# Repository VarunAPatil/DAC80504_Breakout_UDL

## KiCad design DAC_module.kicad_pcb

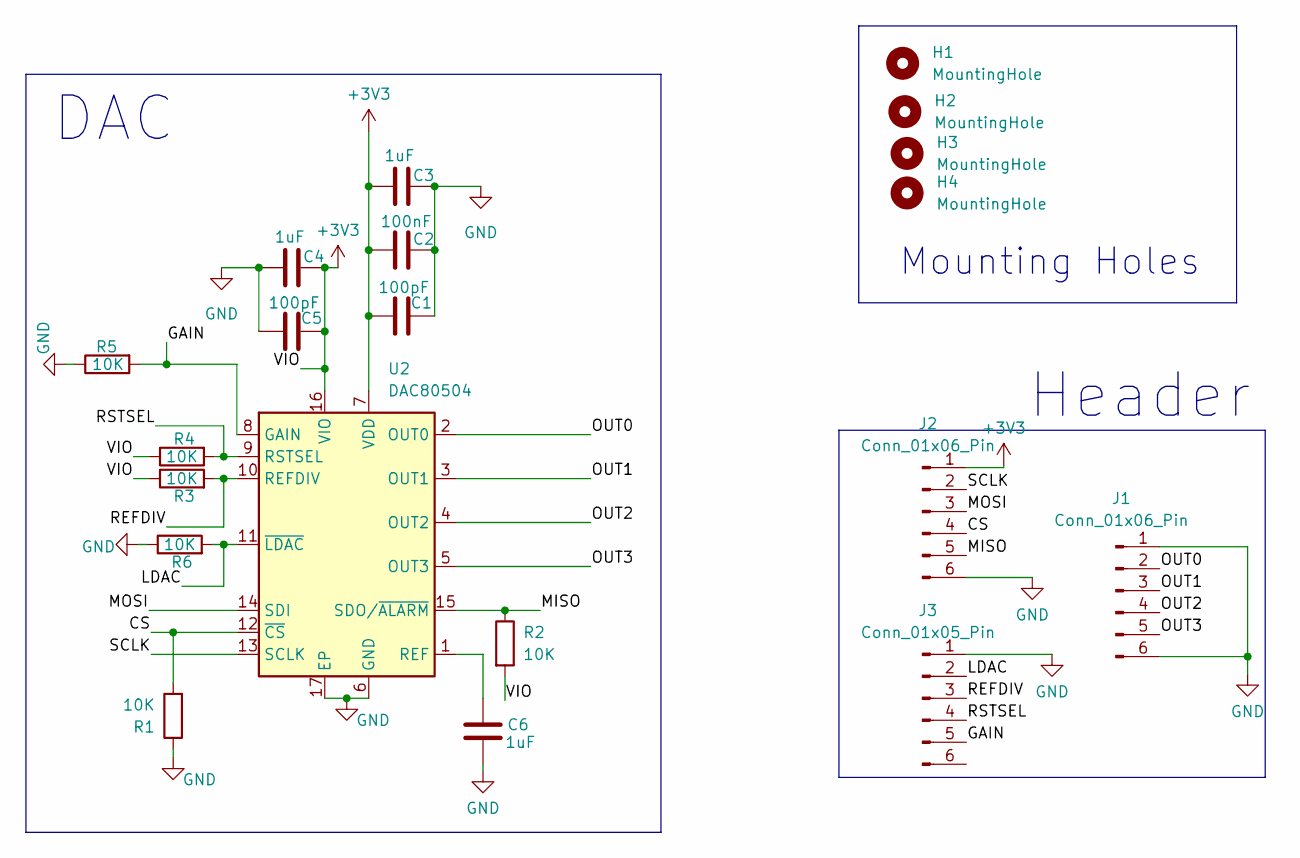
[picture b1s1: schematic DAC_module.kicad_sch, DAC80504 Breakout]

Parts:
C1, C5: 100pF; C_0603_1608Metric
C2: 100nF; C_0603_1608Metric
C3, C4, C6: 1uF; C_0603_1608Metric
H1, H2, H3, H4: MountingHole; MountingHole_2.2mm_M2
J1, J2: Conn_01x06_Pin; PinHeader_1x06_P2.54mm_Vertical
J3: Conn_01x05_Pin; PinHeader_1x05_P2.54mm_Vertical
R1, R2, R3, R4, R5, R6: 10K; R_0603_1608Metric
U2: DAC80504; Texas_RTE0016D_WQFN-16-1EP_3x3mm_P0.5mm_EP0.8x0.8mm_Thermal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

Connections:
+3V3: C1.1, C2.1, C3.1, C4.2, C5.2, J2.1, R2.2, R3.1, R4.1, U2.7 (VDD), U2.16 (VIO)
/CS: J2.4, R1.2, U2.12 (~CS)
/GAIN: J3.5, R5.2, U2.8 (GAIN)
/LDAC: J3.2, R6.2, U2.11 (~LDAC)
/MISO: J2.5, R2.1, U2.15 (SDO/~ALARM)
/MOSI: J2.3, U2.14 (SDI)
/OUT0: J1.2, U2.2 (OUT0)
/OUT1: J1.3, U2.3 (OUT1)
/OUT2: J1.4, U2.4 (OUT2)
/OUT3: J1.5, U2.5 (OUT3)
/REFDIV: J3.3, R3.2, U2.10 (REFDIV)
/RSTSEL: J3.4, R4.2, U2.9 (RSTSEL)
/SCLK: J2.2, U2.13 (SCLK)
GND: C1.2, C2.2, C3.2, C4.1, C5.1, C6.1, J1.1, J1.6, J2.6, J3.1, R1.1, R5.1, R6.1, U2.6 (GND), U2.17 (EP)
unnamed: C6.2, U2.1 (REF)

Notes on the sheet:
Mounting Holes
DAC
Header

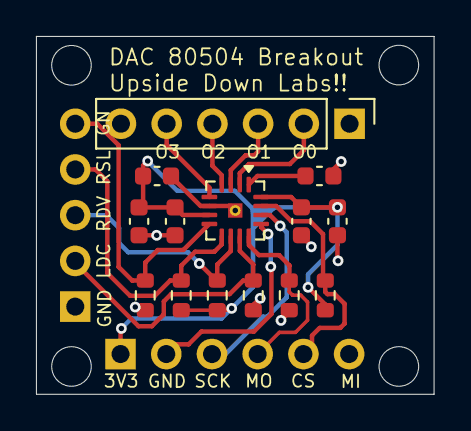
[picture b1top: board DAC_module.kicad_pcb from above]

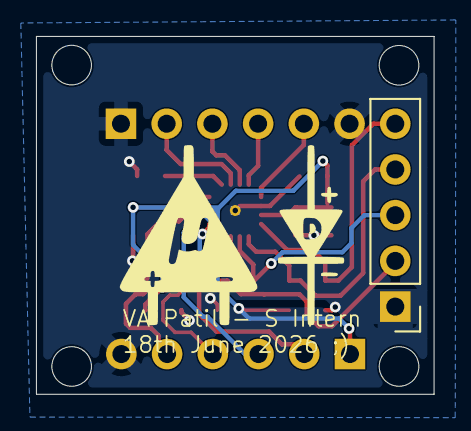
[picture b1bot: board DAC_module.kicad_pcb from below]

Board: 2 copper layers, 22.1 x 19.9 mm, 20 parts (2 on the bottom side), 15 nets.

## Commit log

2026-06-18 Adding PCB files
2026-06-19 Adding files of PCB v0.2
